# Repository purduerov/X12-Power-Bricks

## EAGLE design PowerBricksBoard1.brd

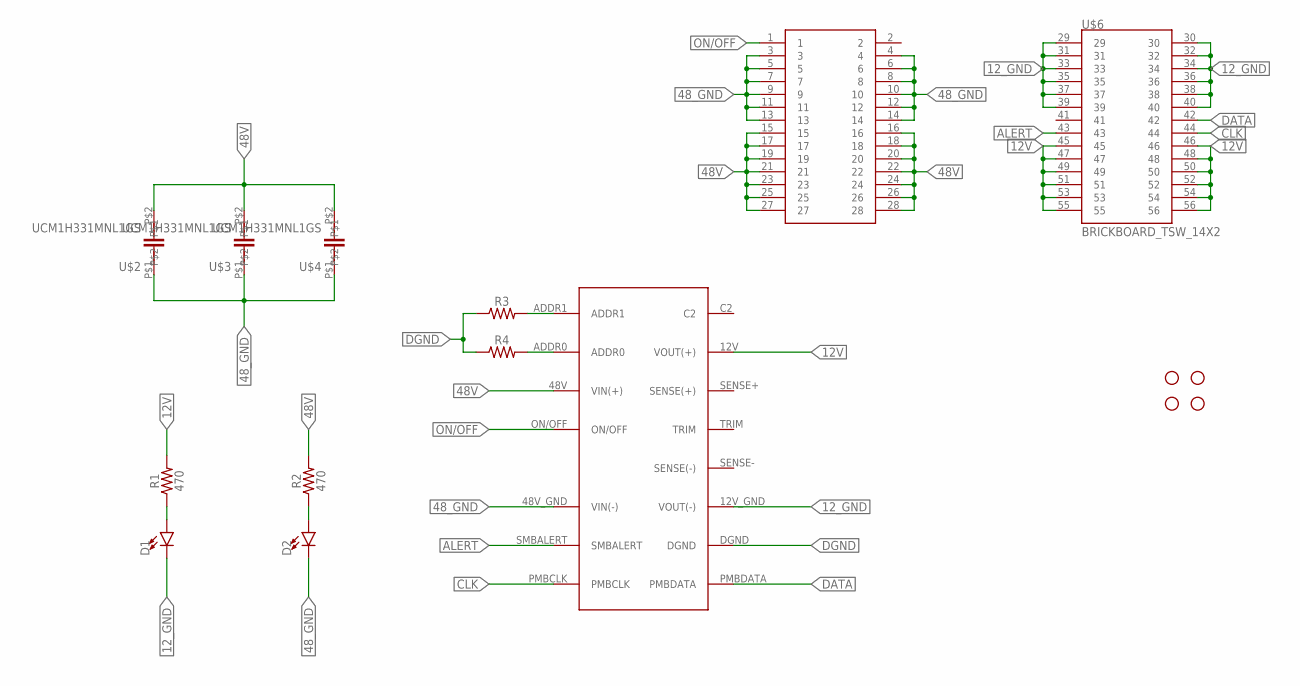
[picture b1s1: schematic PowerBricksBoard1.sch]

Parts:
D1, D2: LED0603; LED-0603
H1, H2, H3, H4: STAND-OFF
R1, R2: 470; 0603
R3, R4: 0603
U$1: Q48SC12050NRDH
U$2, U$3, U$4: UCM1H331MNL1GS
U$6: BRICKBOARD_TSW_14X2

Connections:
12V: R1.2, U$1.12V (VOUT(+)), U$6.45, U$6.46, U$6.47, U$6.48, U$6.49, U$6.50, U$6.51, U$6.52, U$6.53, U$6.54, U$6.55, U$6.56
12_GND: D1.C, U$1.12V_GND (VOUT(-)), U$6.29, U$6.30, U$6.31, U$6.32, U$6.33, U$6.34, U$6.35, U$6.36, U$6.37, U$6.38, U$6.39, U$6.40
48V: R2.2, U$1.48V (VIN(+)), U$2.P$2, U$3.P$2, U$4.P$2, U$6.15, U$6.16, U$6.17, U$6.18, U$6.19, U$6.20, U$6.21, U$6.22, U$6.23, U$6.24, U$6.25, U$6.26, U$6.27, U$6.28
48_GND: D2.C, U$1.48V_GND (VIN(-)), U$2.P$1, U$3.P$1, U$4.P$1, U$6.3, U$6.4, U$6.5, U$6.6, U$6.7, U$6.8, U$6.9, U$6.10, U$6.11, U$6.12, U$6.13, U$6.14
ALERT: U$1.SMBALERT, U$6.43
CLK: U$1.PMBCLK, U$6.44
DATA: U$1.PMBDATA, U$6.42
DGND: R3.1, R4.1, U$1.DGND
unnamed: D1.A, R1.1
unnamed: D2.A, R2.1
unnamed: R3.2, U$1.ADDR1
unnamed: R4.2, U$1.ADDR0
ON/OFF: U$1.ON/OFF, U$6.1

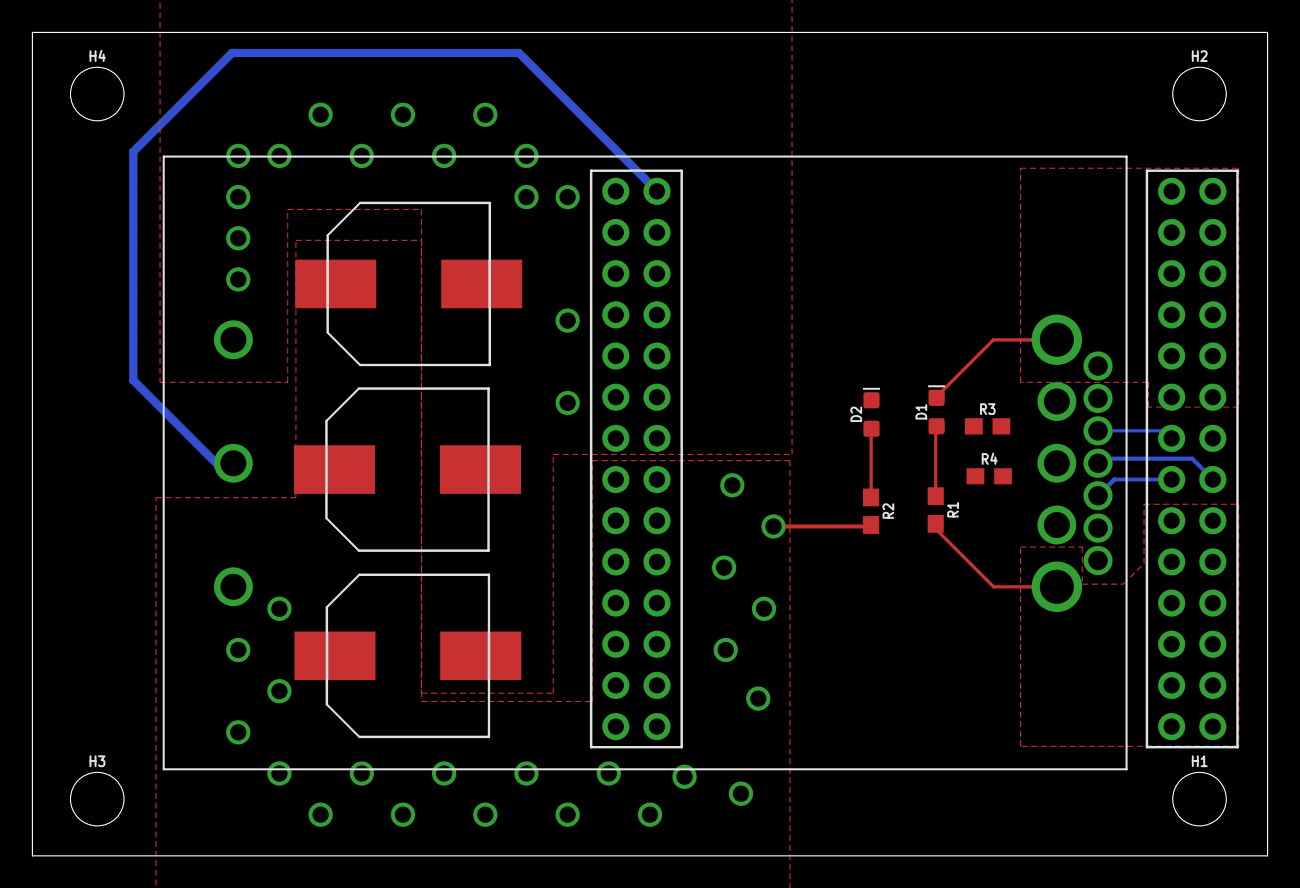
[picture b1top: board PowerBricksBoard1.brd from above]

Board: 2 copper layers, 76.2 x 50.8 mm, 15 parts (0 on the bottom side), 13 nets.

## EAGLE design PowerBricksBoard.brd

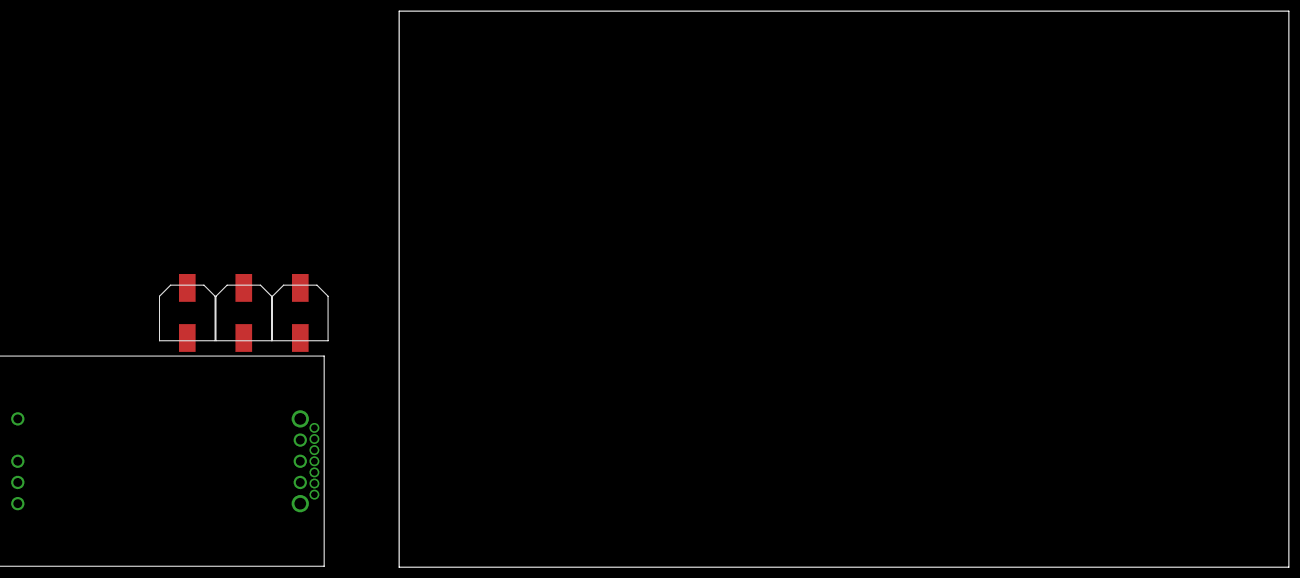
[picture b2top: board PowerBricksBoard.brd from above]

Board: 2 copper layers, 160.0 x 100.0 mm, 4 parts (0 on the bottom side), 2 nets, no tracks yet.

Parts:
U$1: Q48SC12050NRDH
U$2, U$3, U$4: UCM1H331MNL1GS

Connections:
48V: U$1.P$4, U$2.P$1, U$3.P$1, U$4.P$1
48_GND: U$1.P$1, U$2.P$2, U$3.P$2, U$4.P$2

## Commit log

2019-09-25 created schematic
2019-10-16 Added Bricks and Capacitor
2019-11-03 added screw holes
    added screw holes to board and made board slightly bigger.
    (was 3x1.5 now 3x2)
2019-11-07 updated brick part and edited connetors
    had to move connector for capacitor placement
2019-11-09 Updated Brick Board (changed connectors GND & input)
2019-11-09 updated connectors brick board (half routed)
2019-11-19 Board with draft routing
2019-11-19 Fixed DRC error
2019-11-20 Traces need verification
2019-11-21 Bricks updated Alumni Review
2019-11-24 updated led
    Needs to connect trace to 48V and 48_GNd
2019-12-24 finished up
    created names on board
    finished the routing of LED
    ran drc check
2019-12-31 added labels to LEDs
2020-01-01 added spongegar
2020-01-07 Approved DRC issues
2020-09-10 Make schematic and board consistent Revert "Approved DRC issues"
    This reverts commit a0d234d36144a7cc705f185bdd79d5ccd2557d08.
2020-09-12 fixes (sorry for non descriptive commit
2020-09-13 cad for connectors
2020-09-26 Filled caps & ADDR resistors

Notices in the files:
parts and their libraries:
SparkFun-Hardware: Licensing: Creative Commons ShareAlike 4.0 International - https://creativecommons.org/licenses/by-sa/4.0
